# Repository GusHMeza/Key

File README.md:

# KEY

### Copper structure characterization for low-speed designs

Movtivation:

Validate JLC PBC's cheapest controlled impedance 4L board offer for 1 GHz signals.

The goal:

1. Propose common copper structures as 'test cases'.
2. Make the design feel like a template to validate a stackup or stackup change.

Methodology:
1. Capture common copper structures like transitions, stubs and length matching structures.
2. Use standard SMA connectors to interface with a NanoVNA or similar.
3. Measure the desired frequency range and extract S11 and S21 for the different test cases.
4. Evaluate the results and generate design feedback.

### Design History museum

main: First approach to creating a test vehicle that included calibration and a few high-speed tests based on signal integrity problems seen -in scientific papers- in >30 GHz designs.

RevB branch: Major redesign to better reflect the intention of validating low-speed structures. Improves on the calibration section as it now inlcudes a correct SOLT calibration coupon.

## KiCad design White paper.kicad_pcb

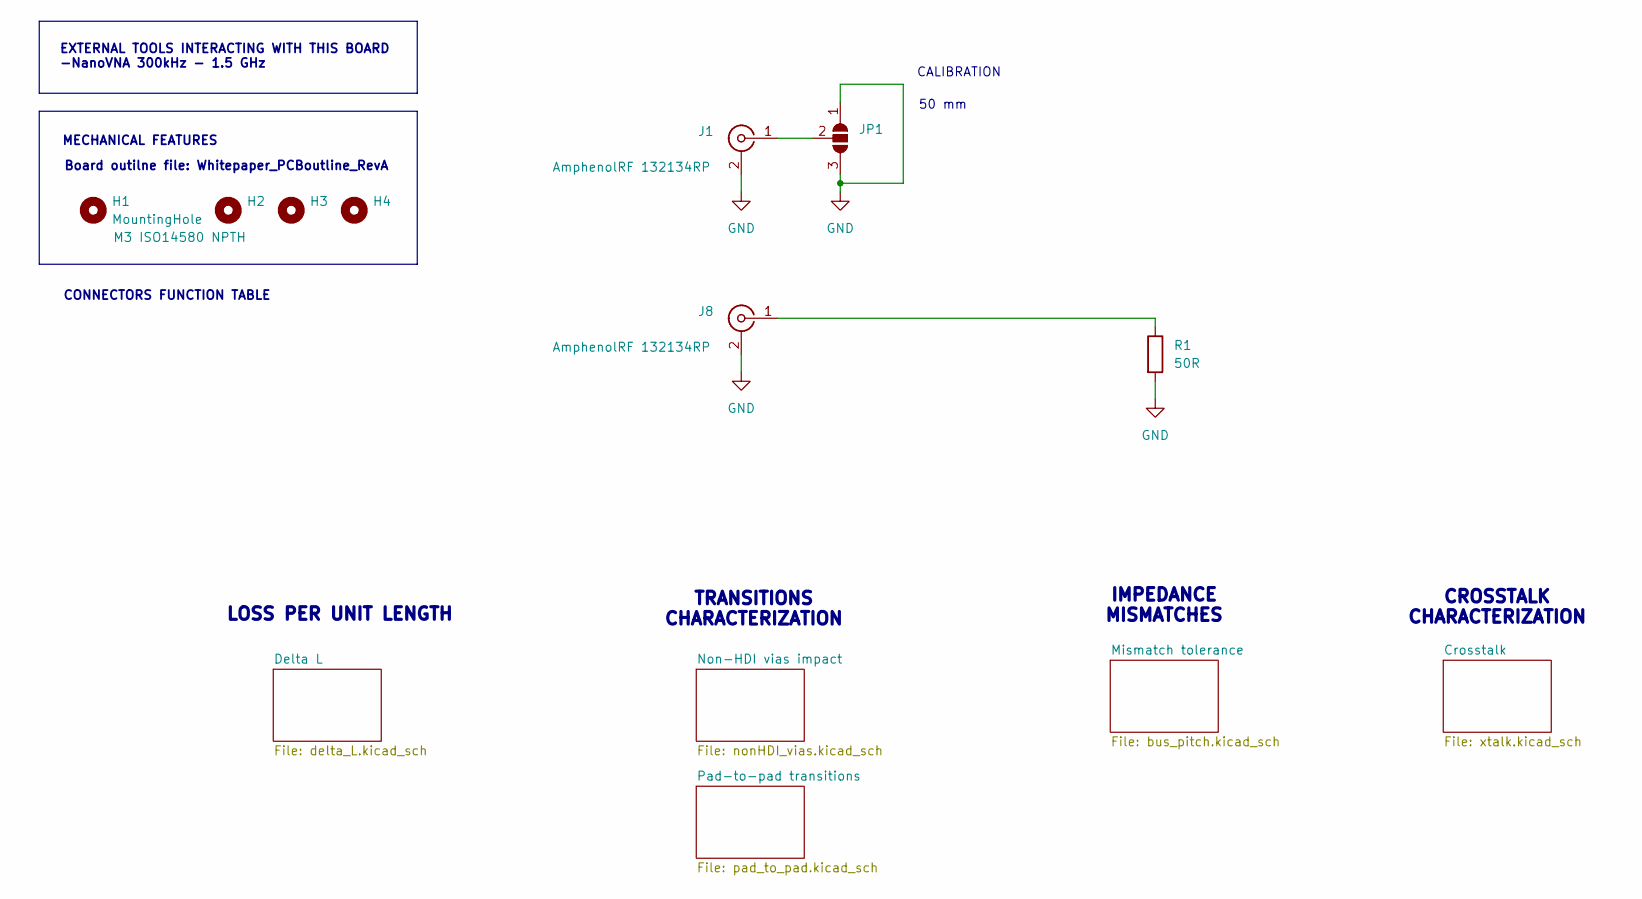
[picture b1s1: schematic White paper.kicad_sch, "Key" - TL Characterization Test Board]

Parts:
H1, H2, H3, H4: MountingHole; MountingHole_3.2mm_M3_ISO14580
J1, J8: Conn_Coaxial; SMA
JP1: SolderJumper_3_Open; SolderJumper-3_P1.3mm_Open_Pad1.0x1.5mm
R1: 50R; R_0603_1608Metric

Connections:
GND: J1.2 (Ext), J8.2 (Ext), JP1.1 (A), JP1.3 (B), R1.2; also elsewhere on the board
unnamed: J1.1 (In), JP1.2 (C)
unnamed 8: J8.1 (In), R1.1; also elsewhere on the board

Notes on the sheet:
TRANSITIONS CHARACTERIZATION
MECHANICAL FEATURES
LOSS PER UNIT LENGTH
IMPEDANCE MISMATCHES
Board outilne file: Whitepaper_PCBoutline_RevA
EXTERNAL TOOLS INTERACTING WITH THIS BOARD -NanoVNA 300kHz - 1.5 GHz
50 mm
CROSSTALK CHARACTERIZATION
CONNECTORS FUNCTION TABLE
CALIBRATION

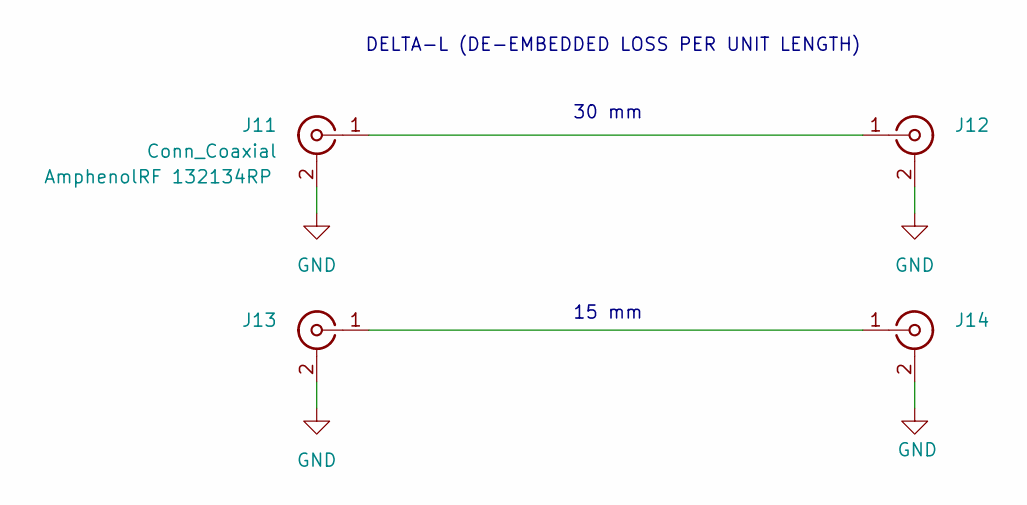
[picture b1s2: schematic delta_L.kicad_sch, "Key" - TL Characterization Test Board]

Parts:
J11, J12, J13, J14: Conn_Coaxial; SMA

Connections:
GND: J11.2 (Ext), J12.2 (Ext), J13.2 (Ext), J14.2 (Ext); also elsewhere on the board
unnamed: J11.1 (In), J12.1 (In)
unnamed: J13.1 (In), J14.1 (In)

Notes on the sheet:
15 mm
30 mm
DELTA-L (DE-EMBEDDED LOSS PER UNIT LENGTH)

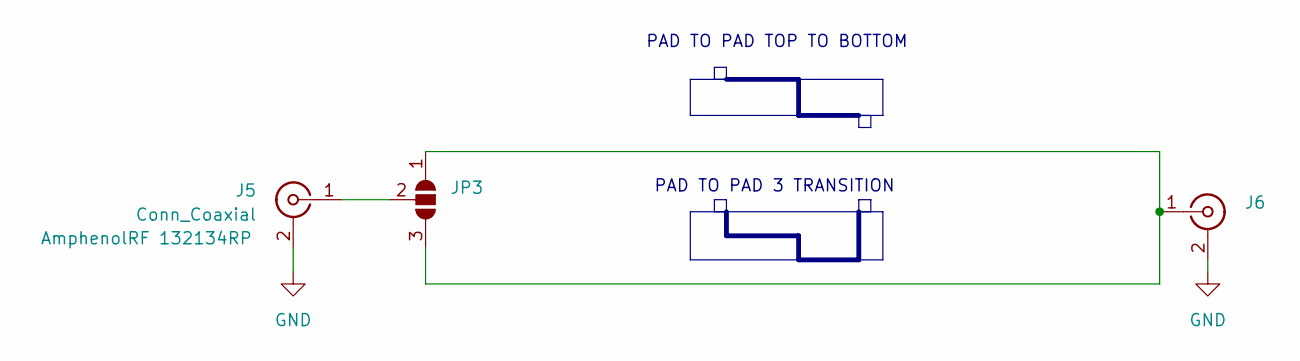
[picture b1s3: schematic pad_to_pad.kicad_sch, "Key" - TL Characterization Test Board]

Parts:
J5, J6: Conn_Coaxial; SMA
JP3: SolderJumper_3_Open; SolderJumper-3_P1.3mm_Open_Pad1.0x1.5mm

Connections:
GND: J5.2 (Ext), J6.2 (Ext); also elsewhere on the board
unnamed: J5.1 (In), JP3.2 (C)
unnamed: J6.1 (In), JP3.1 (A), JP3.3 (B)

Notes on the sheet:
PAD TO PAD TOP TO BOTTOM
PAD TO PAD 3 TRANSITION

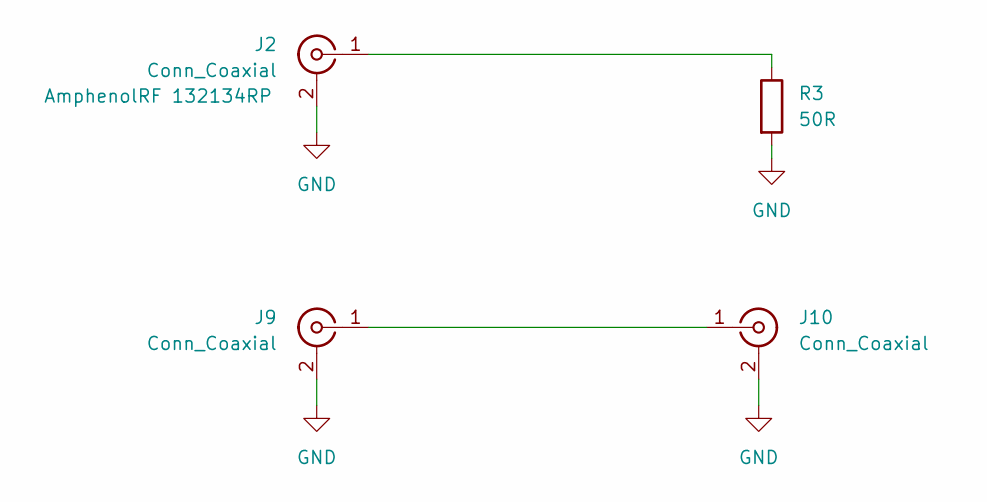
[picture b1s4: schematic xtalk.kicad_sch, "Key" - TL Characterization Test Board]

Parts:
J2, J9, J10: Conn_Coaxial; SMA
R3: 50R; R_0603_1608Metric

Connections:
GND: J2.2 (Ext), J9.2 (Ext), J10.2 (Ext), R3.2; also elsewhere on the board
unnamed 2: J2.1 (In), R3.1; also elsewhere on the board
unnamed: J9.1 (In), J10.1 (In)

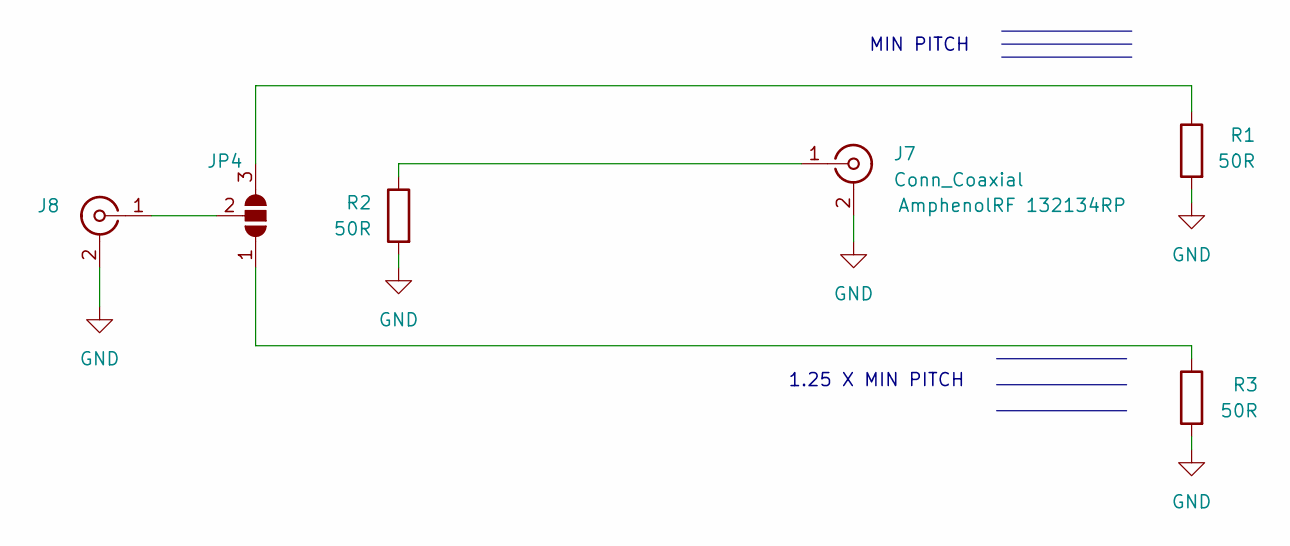
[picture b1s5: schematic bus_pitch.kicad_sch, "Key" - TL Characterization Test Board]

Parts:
J7, J8: Conn_Coaxial; SMA
JP4: SolderJumper_3_Open; SolderJumper-3_P1.3mm_Open_Pad1.0x1.5mm
R1, R2, R3: 50R; R_0603_1608Metric

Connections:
GND: J7.2 (Ext), J8.2 (Ext), R1.2, R2.2, R3.2; also elsewhere on the board
unnamed 2: JP4.1 (A), R3.1; also elsewhere on the board
unnamed: J7.1 (In), R2.1
unnamed: J8.1 (In), JP4.2 (C), JP4.3 (B), R1.1

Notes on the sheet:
1.25 X MIN PITCH
MIN PITCH

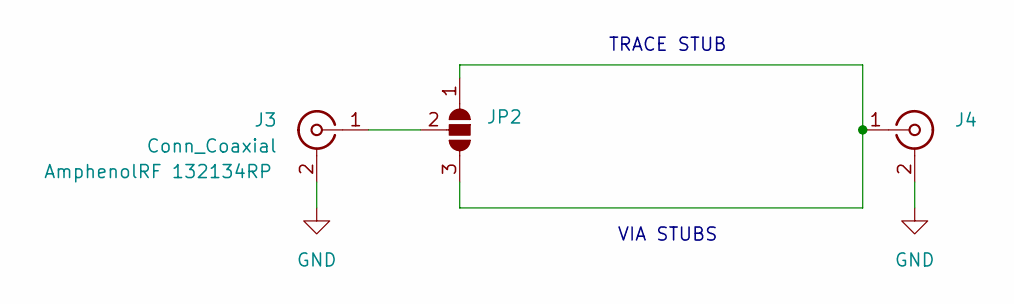
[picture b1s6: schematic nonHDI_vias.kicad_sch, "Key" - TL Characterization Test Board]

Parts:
J3, J4: Conn_Coaxial; SMA
JP2: SolderJumper_3_Open; SolderJumper-3_P1.3mm_Open_Pad1.0x1.5mm

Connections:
GND: J3.2 (Ext), J4.2 (Ext); also elsewhere on the board
unnamed: J3.1 (In), JP2.2 (C)
unnamed: J4.1 (In), JP2.1 (A), JP2.3 (B)

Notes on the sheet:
VIA STUBS
TRACE STUB

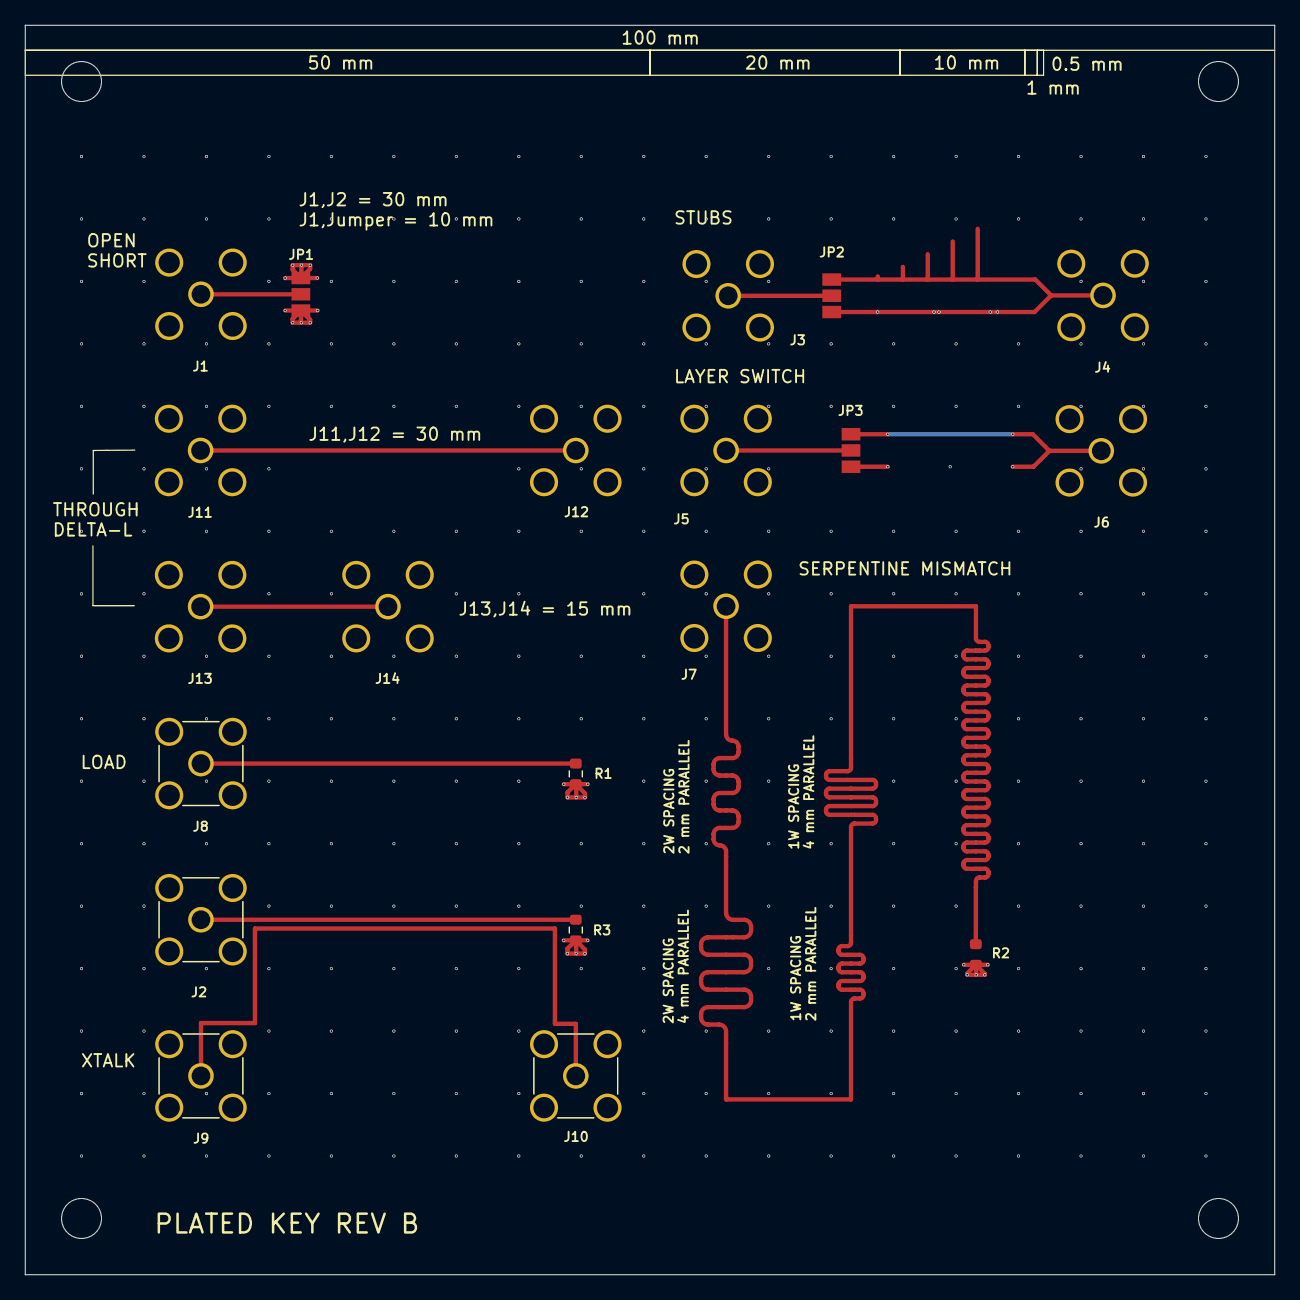
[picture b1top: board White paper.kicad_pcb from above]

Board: 4 copper layers, 100.0 x 100.0 mm, 24 parts (0 on the bottom side), 12 nets.

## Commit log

2026-02-02 Initial commit
    All files
2026-02-02 Rev B
    Added 50R controlled Z, SOLT calibration and more reasonable tests
2026-02-02 Update README.md
    Add pictures
